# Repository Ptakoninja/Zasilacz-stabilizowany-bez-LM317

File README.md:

# Zasilacz-stabilizowany-bez-wykorzystania-LM317
# Regulated power supply without using LM317.
Zasilacz został wykonany w programie Eagle.
Płytka została wykonan z możliwością wsadzenia jej do obudowy dlatego schemat końcowy może różnić się względem shcematu płytki
bezpiecznik jak i transformator znajdują się poza nią tak samo potencjometry
Głównym zamysłem było wykonanie zasilacza bez użycia LM317, założennie zostało spełnione.
kolejnym założeniem było sterowaniem napięcia w zakresie od 0 do 15 V oraz ograniczeniem prądowym od 0 do 2 A 

Przeiwdziane są dodtakowe wyjście na usprawnienie układu wentylaotrem lub woltomierzem oraz amperomierzem wymagającego dodatkowego zasilania

Rezystory R3(RV) oraz RA służą do ustawienia konkretnego napięcienia/natężenia
Schemat końcowy zasilacza wygląda następująco:

**ENG**
The power supply was designed in Eagle software. The PCB was designed to fit into a housing, so the final schematic may differ from the PCB schematic. The fuse and transformer are located outside the PCB. The main idea was to design a power supply without using LM317, and this assumption has been met. Another requirement was to control the voltage in the range of 0 to 15 V and limit the current from 0 to 2 A.

Additional outputs are provided for improving the system with a fan or adding a voltmeter and ammeter requiring extra power supply.

Resistors R3 (RV) and RA are used to set specific voltage/current values. The final schematic of the power supply looks as follows:

schemat wykorzystany do stowrzenia płytki PCB:

**ENG**
The schematic used to create the PCB board is as follows:

Wygląd końcowy płytki z góry:

**ENG**
The final appearance of the PCB from the top:

W przypadku symulacji 
Zasilacz po zmontowaniu działał zadawalająco prąd mieścił się w zakresie 0-1,7A a napięcie od 1,3 do 14,6 dobierając lepszej jakości rezystory można poprawić zakres na bardziej zbliżony do oczekiwanych.
W przypadku Symulacji należy oddzielnie przeprowadić dla stabilizaci  napięcia jak i natężenia bo inaczej trwa długo
dodatkowo w przypadku nateżenia trzeba dodać rezystor na wyjściu układu

**ENG**
In the case of simulation:
After assembly, the power supply worked satisfactorily, with the current ranging from 0 to 1.7A and the voltage from 1.3 to 14.6V. By selecting higher quality resistors, the range can be adjusted to be closer to the expected values.
For simulation purposes, it is advisable to conduct separate simulations for voltage stabilization and current limitation, as combining them can prolong the simulation time. Additionally, for current limitation, a resistor needs to be added at the output of the circuit.

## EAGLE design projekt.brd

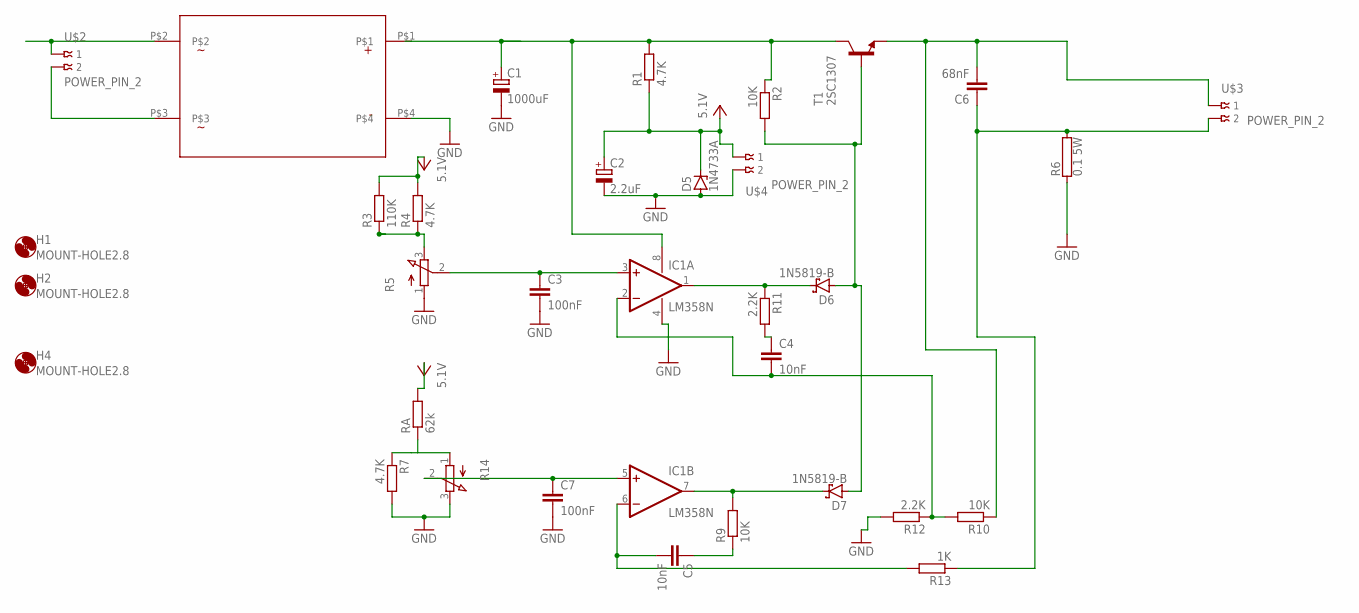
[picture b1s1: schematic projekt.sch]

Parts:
C1: 1000uF; E7,5-18
C2: 2.2uF; E2,5-6E
C3, C7: 100nF; C050-025X075
C4, C5: 10nF; C050-025X075
C6: 68nF; C050-025X075
D5: 1N4733A; DO41Z10
D6, D7: 1N5819-B; DO41-7.6
H1, H2, H4: MOUNT-HOLE2.8; 2,8
IC1: LM358N; DIL08
R1, R4, R7: 4.7K; 0207/10
R2, R9, R10: 10K; 0207/10
R3: 110K; 0207/10
R5, R14: 3RP/1610N
R6: 0.1 5W; KWP333
R11, R12: 2.2K; 0207/10
R13: 1K; 0207/10
RA: 62k; 0207/10
T1: 2SC1307; TO220AV
U$1: GBP201-YAN; GBP201
U$2, U$3, U$4: POWER_PIN_2; PIN2

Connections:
GND: C1.-, C2.-, C3.2, C7.2, D5.A, IC1.4 (V-), R5.1 (A), R6.1, R7.2, R12.2, R14.3 (E), U$1.P$4, U$4.P$2 (2)
unnamed: C6.1, R6.2, R13.1, U$3.P$2 (2)
unnamed: C1.+, IC1.8 (V+), R1.2, R2.1, T1.2 (C), U$1.P$1
unnamed: C4.1, R11.2
unnamed: R3.1, R4.1, R5.3 (E)
unnamed: D7.C, IC1.7 (OUT), R9.2
unnamed: C5.1, R9.1
unnamed: R7.1, R14.1 (A), RA.1
unnamed: C3.1, IC1.3 (+IN), R5.2 (S)
unnamed: C7.1, IC1.5 (+IN), R14.2 (S)
unnamed: D6.C, IC1.1 (OUT), R11.1
unnamed: C4.2, IC1.2 (-IN), R10.2, R12.1
unnamed: D6.A, D7.A, R2.2, T1.1 (B)
unnamed: U$1.P$2, U$2.P$1 (1)
unnamed: C5.2, IC1.6 (-IN), R13.2
unnamed: C6.2, R10.1, T1.3 (E), U$3.P$1 (1)
unnamed: U$1.P$3, U$2.P$2 (2)
VCC: C2.+, D5.C, R1.1, R3.2, R4.2, RA.2, U$4.P$1 (1)

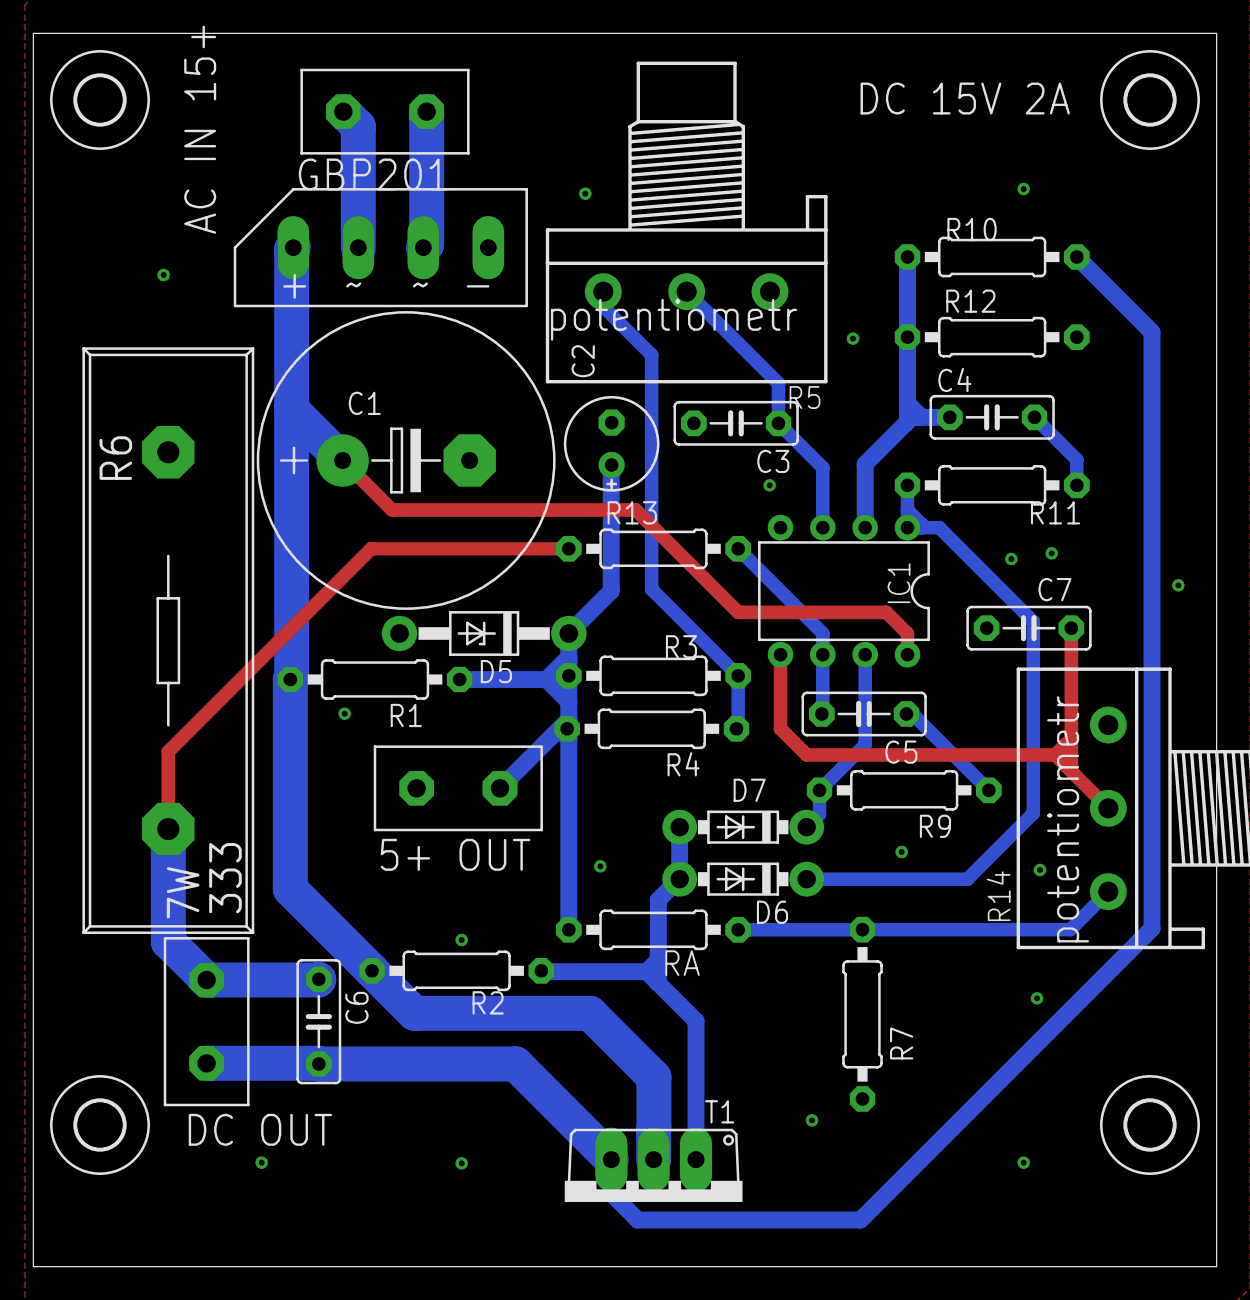
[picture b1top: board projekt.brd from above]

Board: 2 copper layers, 71.0 x 74.0 mm, 34 parts (0 on the bottom side), 18 nets.

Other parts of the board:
H3: MOUNT-HOLE2.8; 2,8

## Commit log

2024-03-19 działanie schematu
2024-03-19 Schemat końcowy całego zasilacza
    W między czasie była dodatkowa modyfikacja pomiędzy bezpiecznikiem a transformatorem jest przycisk włączający
2024-03-19 Rename image.png to Schemati.png
2024-03-19 symulacja ltspice
